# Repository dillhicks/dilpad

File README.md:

# dilpad: Hotswap Numpad/Macropad with QMK Support

## Summary

**Dilpad** is a simple, easy to build numpad that is loosely based on the [Dumbpad](https://github.com/imchipwood/dumbpad). Initially created as a fork of the [Dumbpad combo_oled](https://github.com/imchipwood/dumbpad/tree/master/combo_oled), but adds hotswap switches, screw holes for mounting the PCB to the case, and moved everything to the right. It was decided at that point to simply make another board to learn how to build keyboards from scratch!

This board presents a great introduction to making keyboards, and soldering to those who are new. The dilpad also sounds surprisingly good with a plate/shroud and case that resonates well. The dilpad was also designed with a little bit more space to the edges of the PCB, which can open the doors for some interesting mounting options, such as gasket mounting if anyone wants to try that.

## Features

* **QMK & VIA Support**
  
* **Hotswap Sockets**

* **Rotary Encoder**
  
* **Through-Hole Components: Designed for straightforward soldering.**

## Parts List

The following components are needed to build the dilpad. Costs have been added for convenience (based off of 2024 Aliexpress prices)

### Mandatory Components

| Component                                                  | Quantity | Approx. Cost for 1 dilpad ($)                     |
| ---------------------------------------------------------- | -------- | ------------------------------------------------- |
| Dilpad PCB                                                 | 1        | 2.5                                               |
| MX-style mechanical switches                               | 16       | 4                                                 |
| Kailh CPG151101S11 hotswap sockets                         | 16       | 3                                                 |
| MX-style keycaps                                           | 16       | 2.5 (or use those leftover with your keycap set!) |
| 1N4148 diodes (through-hole)                               | 17       | 0.5                                               |
| Arduino Pro Micro or a pin-compatible ATmega32u4-based MCU | 1        | 3.5                                               |

### Optional Components

| Component                           | Quantity | Approx. Cost for 1 dilpad ($) |
| ----------------------------------- | -------- | ----------------------------- |
| EC11 rotary encoder with pushbutton | 1        | 1                             |
| SSD1306 OLED                        | 1        | 2                             |
| 6mm push button                     | 1        | .25                           |

In total, it should cost less than 25 dollars, even cheaper if you decide to forgo the OLED and rotary encoder!

### Tools Needed
* Soldering Iron

* Flush Wire Cutters

* Kapton Tape (to insulate the bottom of the OLED)

## Assembly Instructions

I reccomend to solder the components in the following order to the starting from the back side of the PCB:

1. Hotswap Sockets (insert on the back, soldered from the back)
2. Diodes (insert on the front, solder from the back, then cut off diode leads)
3. Arduino Pro Micro (insert on the front, solder from the back, then cut off leads)
4. Rotary Encoder (insert on the front, solder from the back)
5. OLED (Insert on the front, elevate over the Pro Micro, then solder from the back)

Flash Your Firmware:

1. Download the .hex file included in the firmware folder, I reccomend the dilpad_via.hex file.
2. Install QMK Toolbox, or another .hex flashing tool such as avrdude
3. Turn on Auto-Flash in QMK Toolbox, or find what COM Port is used when the Pro Micro is reset in the next step
4. Reset the Pro Micro by shorting GND and RESET, or if the 6mm button is installed, press the button
5. QMK Toolbox should the flash the firmware, or start avrdude immediately after resetting, the firmware should then flash, and should be ready to go!

## Case and Plate

[**Printables**](https://www.printables.com/model/764488-dilpad-case-and-plate)

## TODO

- [ ] Add Firmware to QMK and VIA for official support

- [ ] Make version of shroud without rotary encoder and oled

- [ ] Add additional tools to OLED

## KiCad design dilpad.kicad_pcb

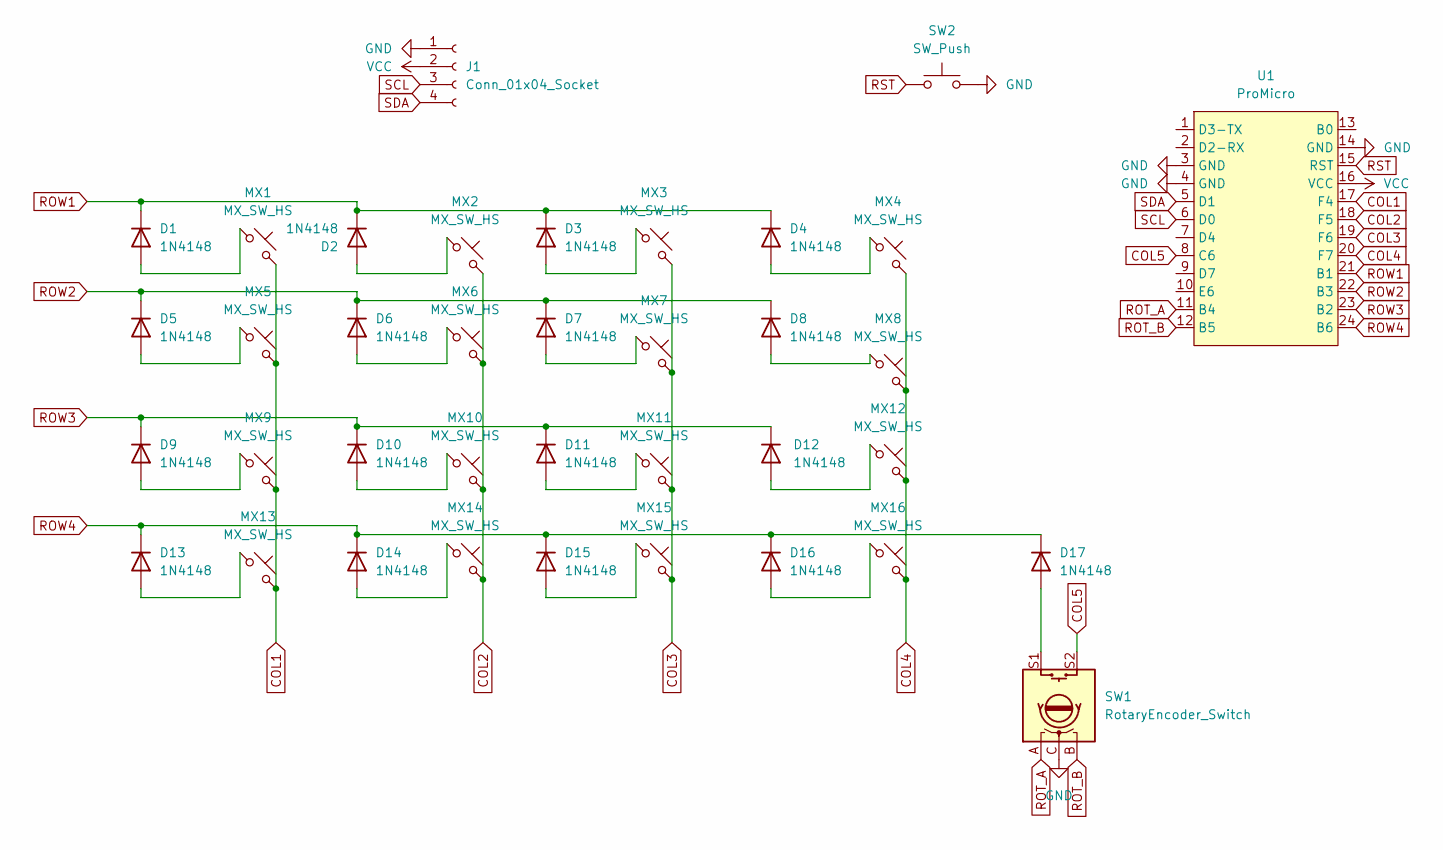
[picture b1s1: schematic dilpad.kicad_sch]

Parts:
D1, D2, D3, D4, D5, D6, D7, D8, D9, D10, D11, D12, D13, D14, D15, D16, D17: 1N4148; D_DO-35_SOD27_P7.62mm_Horizontal
J1: Conn_01x04_Socket; PinHeader_1x04_P2.54mm_Vertical
MX1, MX2, MX3, MX4, MX5, MX6, MX7, MX8, MX9, MX10, MX11, MX12, MX13, MX14, MX15, MX16: MX_SW_HS; SW_MX_HS_1u
SW1: RotaryEncoder_Switch; ROT_Alps_EC11E-Switch
SW2: SW_Push; SW_PUSH_6mm_H8mm
U1: ProMicro; ProMicro_USBup

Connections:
COL1: MX1.2, MX5.2, MX9.2, MX13.2, U1.17 (F4)
COL2: MX2.2, MX6.2, MX10.2, MX14.2, U1.18 (F5)
COL3: MX3.2, MX7.2, MX11.2, MX15.2, U1.19 (F6)
COL4: MX4.2, MX8.2, MX12.2, MX16.2, U1.20 (F7)
COL5: SW1.S2, U1.8 (C6)
GND: J1.1, SW1.C, SW2.2, U1.3 (GND), U1.4 (GND), U1.14 (GND)
unnamed: D1.2 (A), MX1.1
unnamed: D2.2 (A), MX2.1
unnamed: D3.2 (A), MX3.1
unnamed: D4.2 (A), MX4.1
unnamed: D5.2 (A), MX5.1
unnamed: D6.2 (A), MX6.1
unnamed: D7.2 (A), MX7.1
unnamed: D8.2 (A), MX8.1
unnamed: D9.2 (A), MX9.1
unnamed: D10.2 (A), MX10.1
unnamed: D11.2 (A), MX11.1
unnamed: D12.2 (A), MX12.1
unnamed: D13.2 (A), MX13.1
unnamed: D14.2 (A), MX14.1
unnamed: D15.2 (A), MX15.1
unnamed: D16.2 (A), MX16.1
unnamed: D17.2 (A), SW1.S1
ROT_A: SW1.A, U1.11 (B4)
ROT_B: SW1.B, U1.12 (B5)
ROW1: D1.1 (K), D2.1 (K), D3.1 (K), D4.1 (K), U1.21 (B1)
ROW2: D5.1 (K), D6.1 (K), D7.1 (K), D8.1 (K), U1.22 (B3)
ROW3: D9.1 (K), D10.1 (K), D11.1 (K), D12.1 (K), U1.23 (B2)
ROW4: D13.1 (K), D14.1 (K), D15.1 (K), D16.1 (K), D17.1 (K), U1.24 (B6)
RST: SW2.1, U1.15 (RST)
SCL: J1.3, U1.6 (D0)
SDA: J1.4, U1.5 (D1)
VCC: J1.2, U1.16 (VCC)

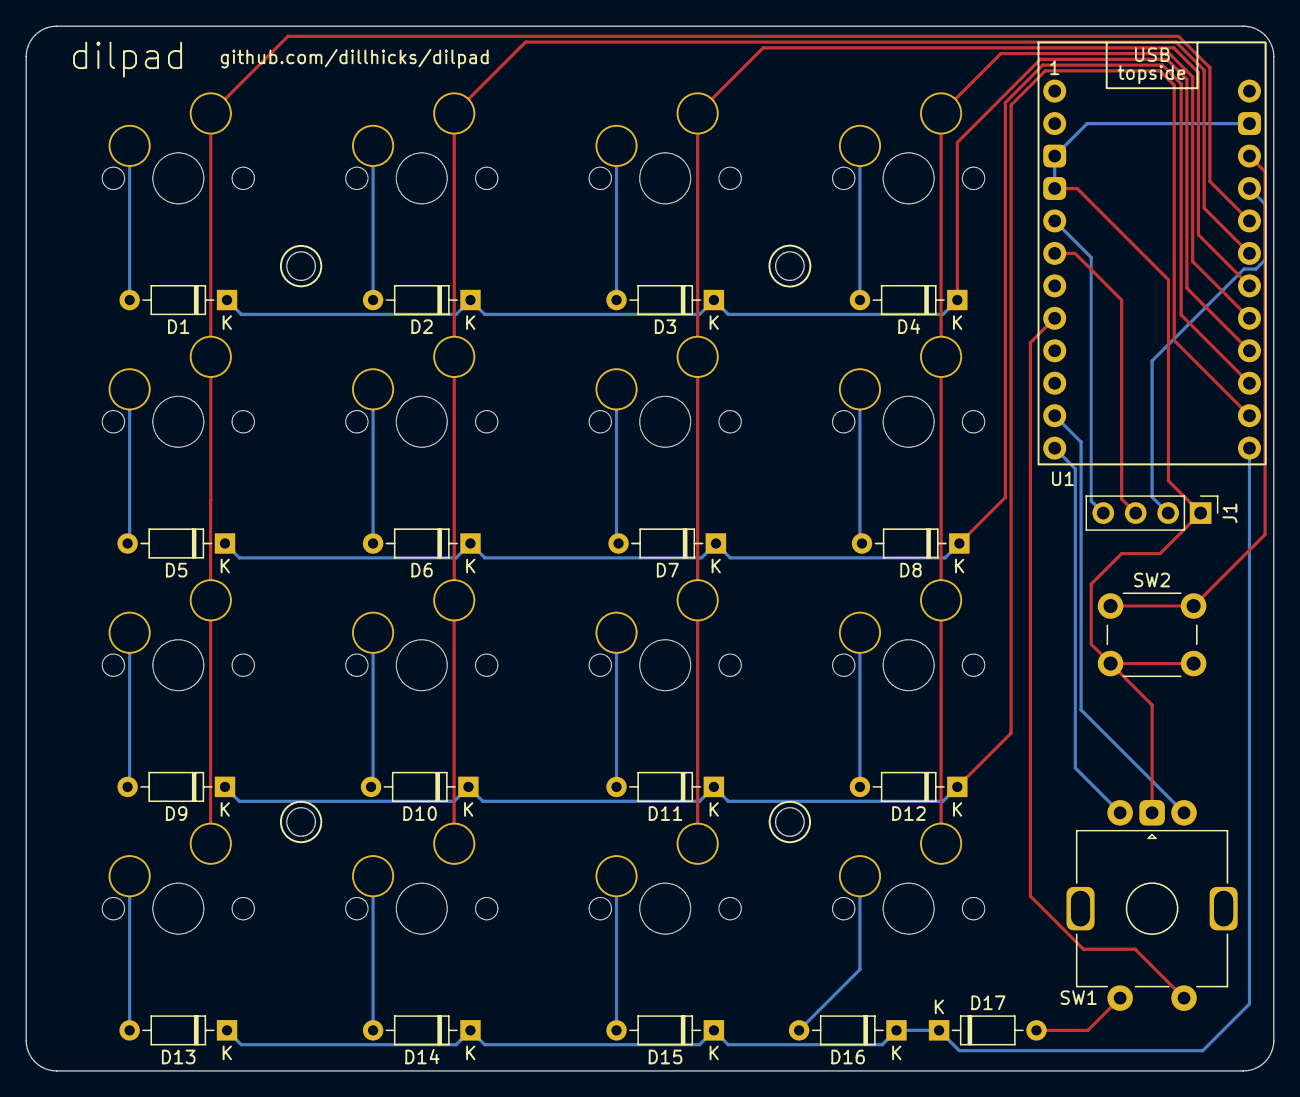
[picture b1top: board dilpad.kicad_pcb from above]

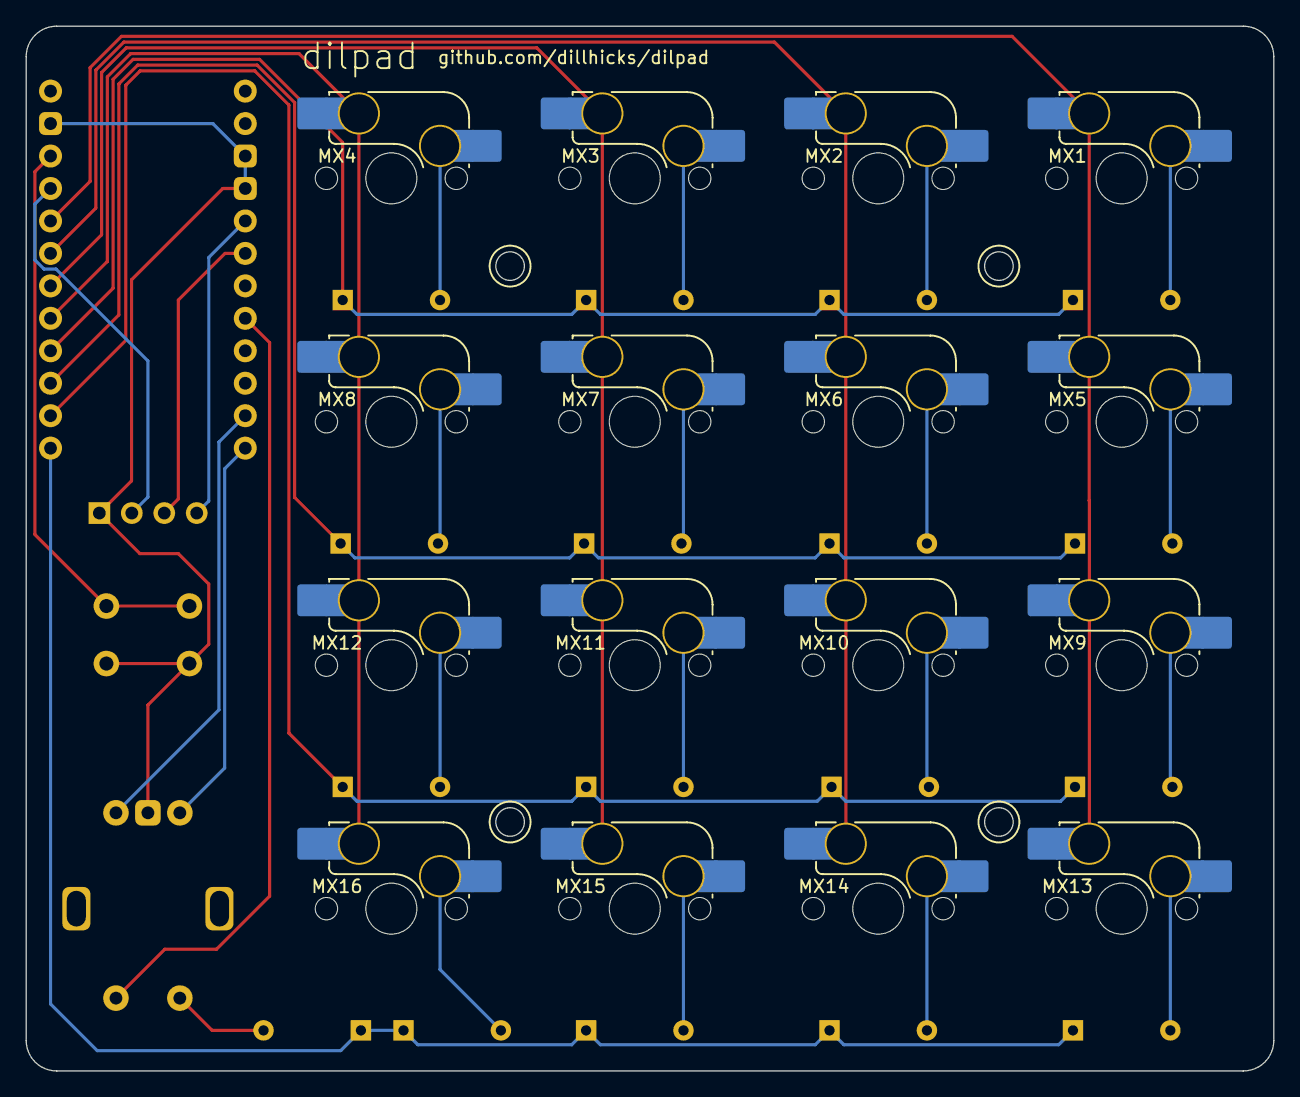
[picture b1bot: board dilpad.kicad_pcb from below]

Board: 2 copper layers, 97.6 x 81.8 mm, 37 parts (16 on the bottom side), 33 nets.

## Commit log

2024-02-14 Update Readme, add images, add firmware files
2024-02-14 Update formatting and add TODO
